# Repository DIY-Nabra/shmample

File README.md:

Sh'mample
=========

Sh'mample is a shift register driven sample and hold sequencer, capable of rungling.
Inspired in equal parts by the Ciat-Lonbarde Man with the Red Steam, and the Buchla 264.

For use with Ciat-Lonbarde instruments.

[Guide](assets/guide.md)

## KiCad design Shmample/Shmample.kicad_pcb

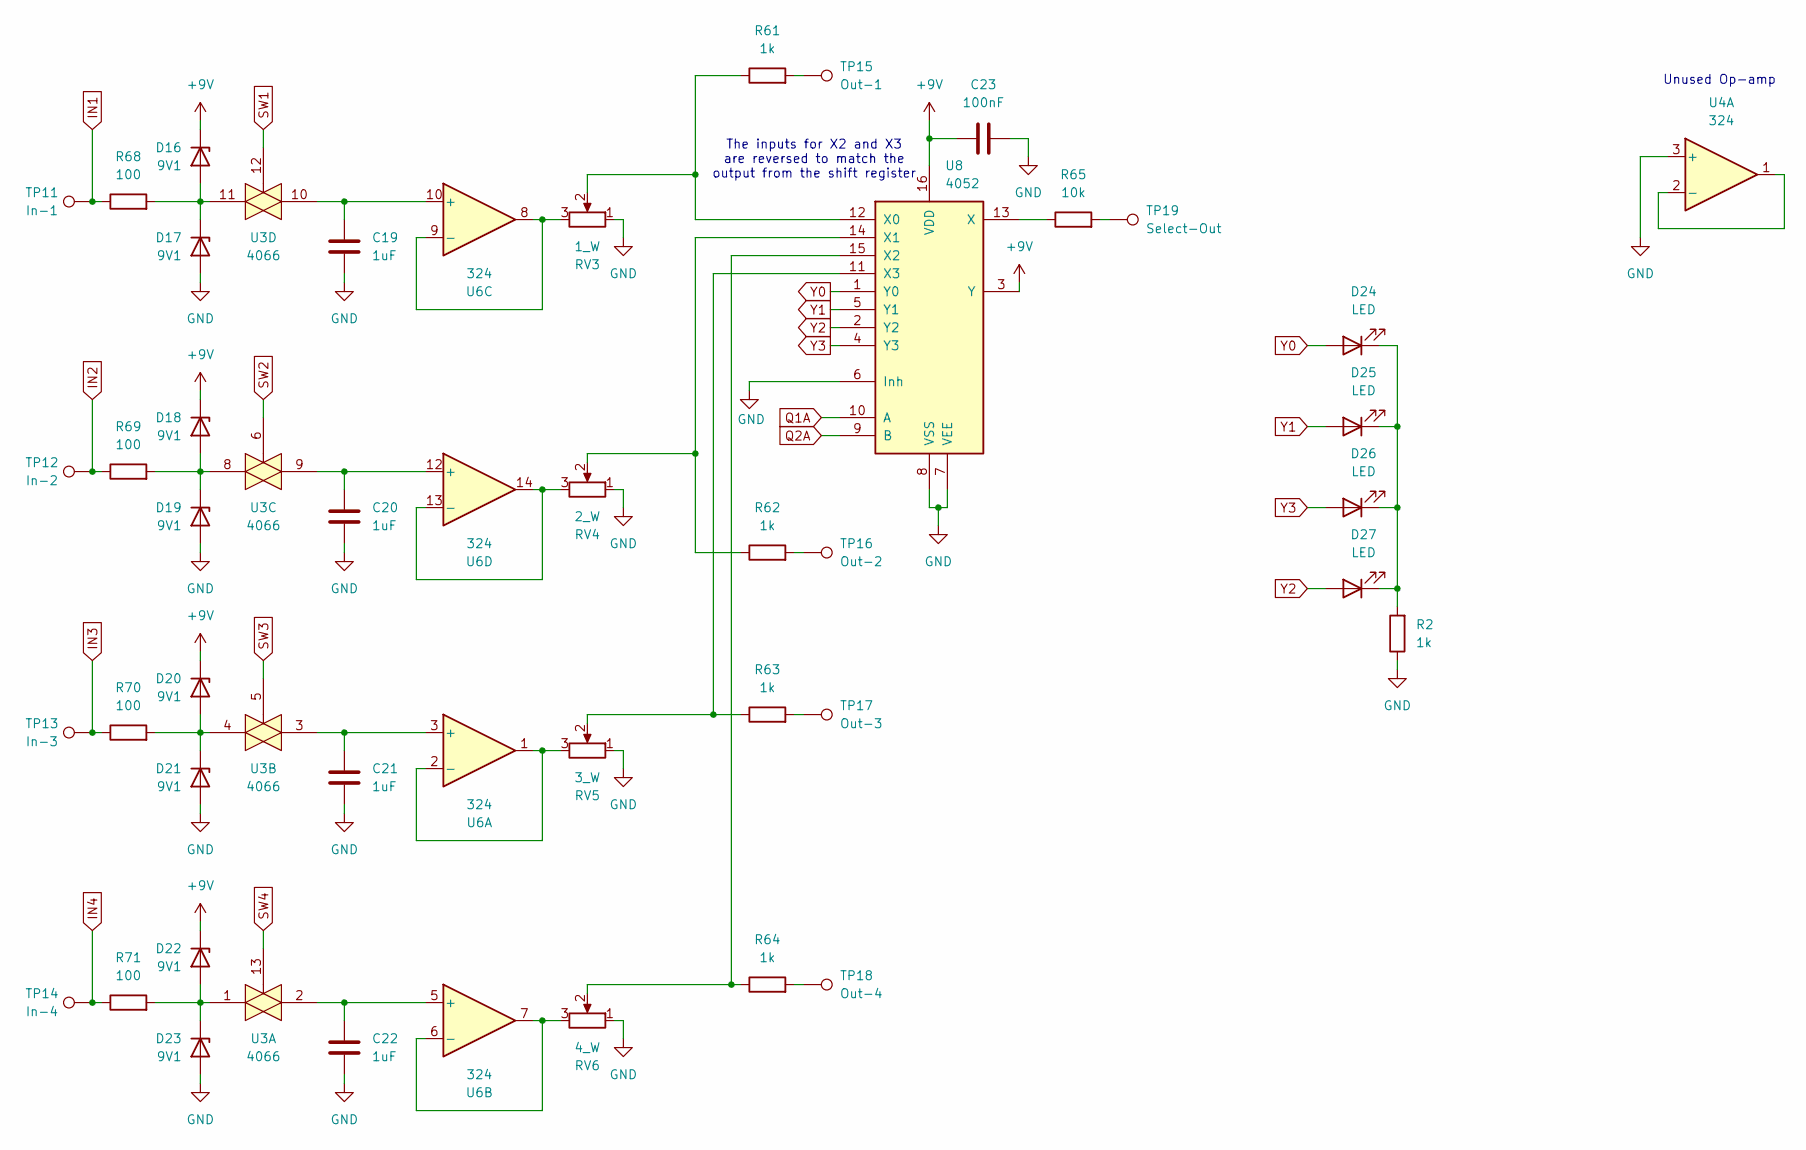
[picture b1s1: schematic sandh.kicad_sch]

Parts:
C19, C20, C21, C22: 1uF; cpoly105
C23: 100nF; cpoly104_small
D16, D17, D18, D19, D20, D21, D22, D23: 9V1; doz3
D24, D25, D26, D27: LED; led
R2, R61, R62, R63, R64: 1k; r3
R65: 10k; r3
R68, R69, R70, R71: 100; r3
RV3: 1_W; wnob1
RV4: 2_W; wnob2
RV5: 3_W; wnob3
RV6: 4_W; wnob4
TP11: In-1; wsquin
TP12: In-2; wsqout
TP13: In-3; wsqu3in
TP14: In-4; wsqu4in
TP15: Out-1; wtrin
TP16: Out-2; wtrin2
TP17: Out-3; wtrin3
TP18: Out-4; wtrin4
TP19: Select-Out; wsqout
U3: 4066; dip14
U4, U6: 324; dip14
U8: 4052; dip16

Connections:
+9V: C23.1, D16.1 (K), D18.1 (K), D20.1 (K), D22.1 (K), U8.3 (Y), U8.16 (VDD); also elsewhere on the board
GND: C19.2, C20.2, C21.2, C22.2, C23.2, D17.2 (A), D19.2 (A), D21.2 (A), D23.2 (A), R2.1, RV3.1, RV4.1, RV5.1, RV6.1, U4.3 (+), U8.6 (Inh), U8.7 (VEE), U8.8 (VSS); also elsewhere on the board
IN1: R68.1, TP11.1
IN2: R69.1, TP12.1
IN3: R70.1, TP13.1
IN4: R71.1, TP14.1
unnamed: D16.2 (A), D17.1 (K), R68.2, U3.11
unnamed: D18.2 (A), D19.1 (K), R69.2, U3.8
unnamed: D20.2 (A), D21.1 (K), R70.2, U3.4
unnamed: D22.2 (A), D23.1 (K), R71.2, U3.1
unnamed: D24.1 (K), D25.1 (K), D26.1 (K), D27.1 (K), R2.2
unnamed: R61.2, TP15.1
unnamed: R62.2, TP16.1
unnamed: R63.2, TP17.1
unnamed: R64.2, TP18.1
unnamed: R65.2, TP19.1
unnamed: U4.1, U4.2 (-)
unnamed: C21.1, U3.3, U6.3 (+)
unnamed: RV5.3, U6.1, U6.2 (-)
unnamed: C22.1, U3.2, U6.5 (+)
unnamed: RV6.3, U6.6 (-), U6.7
unnamed: C19.1, U3.10, U6.10 (+)
unnamed: RV3.3, U6.8, U6.9 (-)
unnamed: C20.1, U3.9, U6.12 (+)
unnamed: RV4.3, U6.13 (-), U6.14
unnamed: R61.1, RV3.2, U8.12 (X0)
unnamed: R62.1, RV4.2, U8.14 (X1)
unnamed: R64.1, RV6.2, U8.15 (X2)
unnamed: R63.1, RV5.2, U8.11 (X3)
unnamed: R65.1, U8.13 (X)
Q1A: U8.10 (A); also elsewhere on the board
Q2A: U8.9 (B); also elsewhere on the board
SW1: U3.12; also elsewhere on the board
SW2: U3.6; also elsewhere on the board
SW3: U3.5; also elsewhere on the board
SW4: U3.13; also elsewhere on the board
Y0: D24.2 (A), U8.1 (Y0)
Y1: D25.2 (A), U8.5 (Y1)
Y2: D27.2 (A), U8.2 (Y2)
Y3: D26.2 (A), U8.4 (Y3)

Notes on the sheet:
The inputs for X2 and X3 are reversed to match the output from the shift register
Unused Op-amp

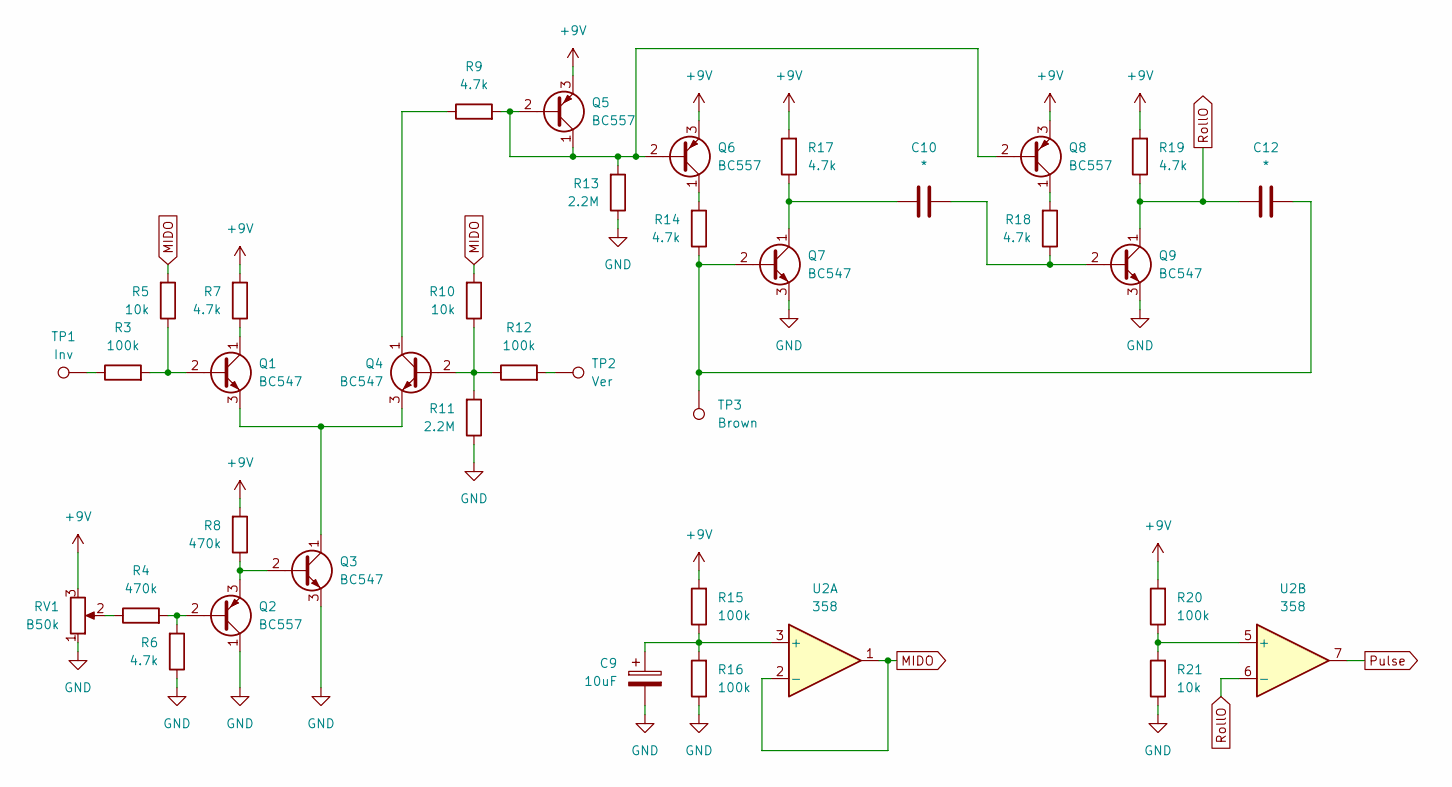
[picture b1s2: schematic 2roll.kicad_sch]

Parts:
C9: 10uF; cel1
C10, C12: *; chairy
Q1, Q3, Q4, Q7, Q9: BC547; qnpn
Q2, Q5, Q6, Q8: BC557; qpnp
R3, R12, R15, R16, R20: 100k; r3
R4, R8: 470k; r3
R5, R10, R21: 10k; r3
R6, R7, R9, R14, R17, R18, R19: 4.7k; r3
R11, R13: 2.2M; r3
RV1: B50k; wnob
TP1: Inv; wtrin2
TP2: Ver; wtrin
TP3: Brown; wsquin
U2: 358; dip8

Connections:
+9V: Q5.3 (E), Q6.3 (E), Q8.3 (E), R7.2, R8.2, R15.2, R17.2, R19.2, R20.2, RV1.3; also elsewhere on the board
GND: C9.2, Q2.1 (C), Q3.3 (E), Q7.3 (E), Q9.3 (E), R6.1, R11.1, R13.1, R16.1, R21.1, RV1.1; also elsewhere on the board
MIDO: R5.2, R10.2, U2.1, U2.2 (-); also elsewhere on the board
unnamed: Q1.2 (B), R3.2, R5.1
unnamed: Q1.1 (C), R7.1
unnamed: Q1.3 (E), Q3.1 (C), Q4.3 (E)
unnamed: Q2.2 (B), R4.2, R6.2
unnamed: Q2.3 (E), Q3.2 (B), R8.1
unnamed: Q4.2 (B), R10.1, R11.2, R12.1
unnamed: Q4.1 (C), R9.1
unnamed: Q5.1 (C), Q5.2 (B), Q6.2 (B), Q8.2 (B), R9.2, R13.2
unnamed: Q6.1 (C), R14.2
unnamed: C12.2, Q7.2 (B), R14.1, TP3.1
unnamed: C10.1, Q7.1 (C), R17.1
unnamed: Q8.1 (C), R18.2
unnamed: C10.2, Q9.2 (B), R18.1
unnamed: R3.1, TP1.1
unnamed: R4.1, RV1.2
unnamed: R12.2, TP2.1
unnamed: C9.1, R15.1, R16.2, U2.3 (+)
unnamed: R20.1, R21.2, U2.5 (+)
Pulse: U2.7; also elsewhere on the board
RollO: C12.1, Q9.1 (C), R19.1, U2.6 (-)

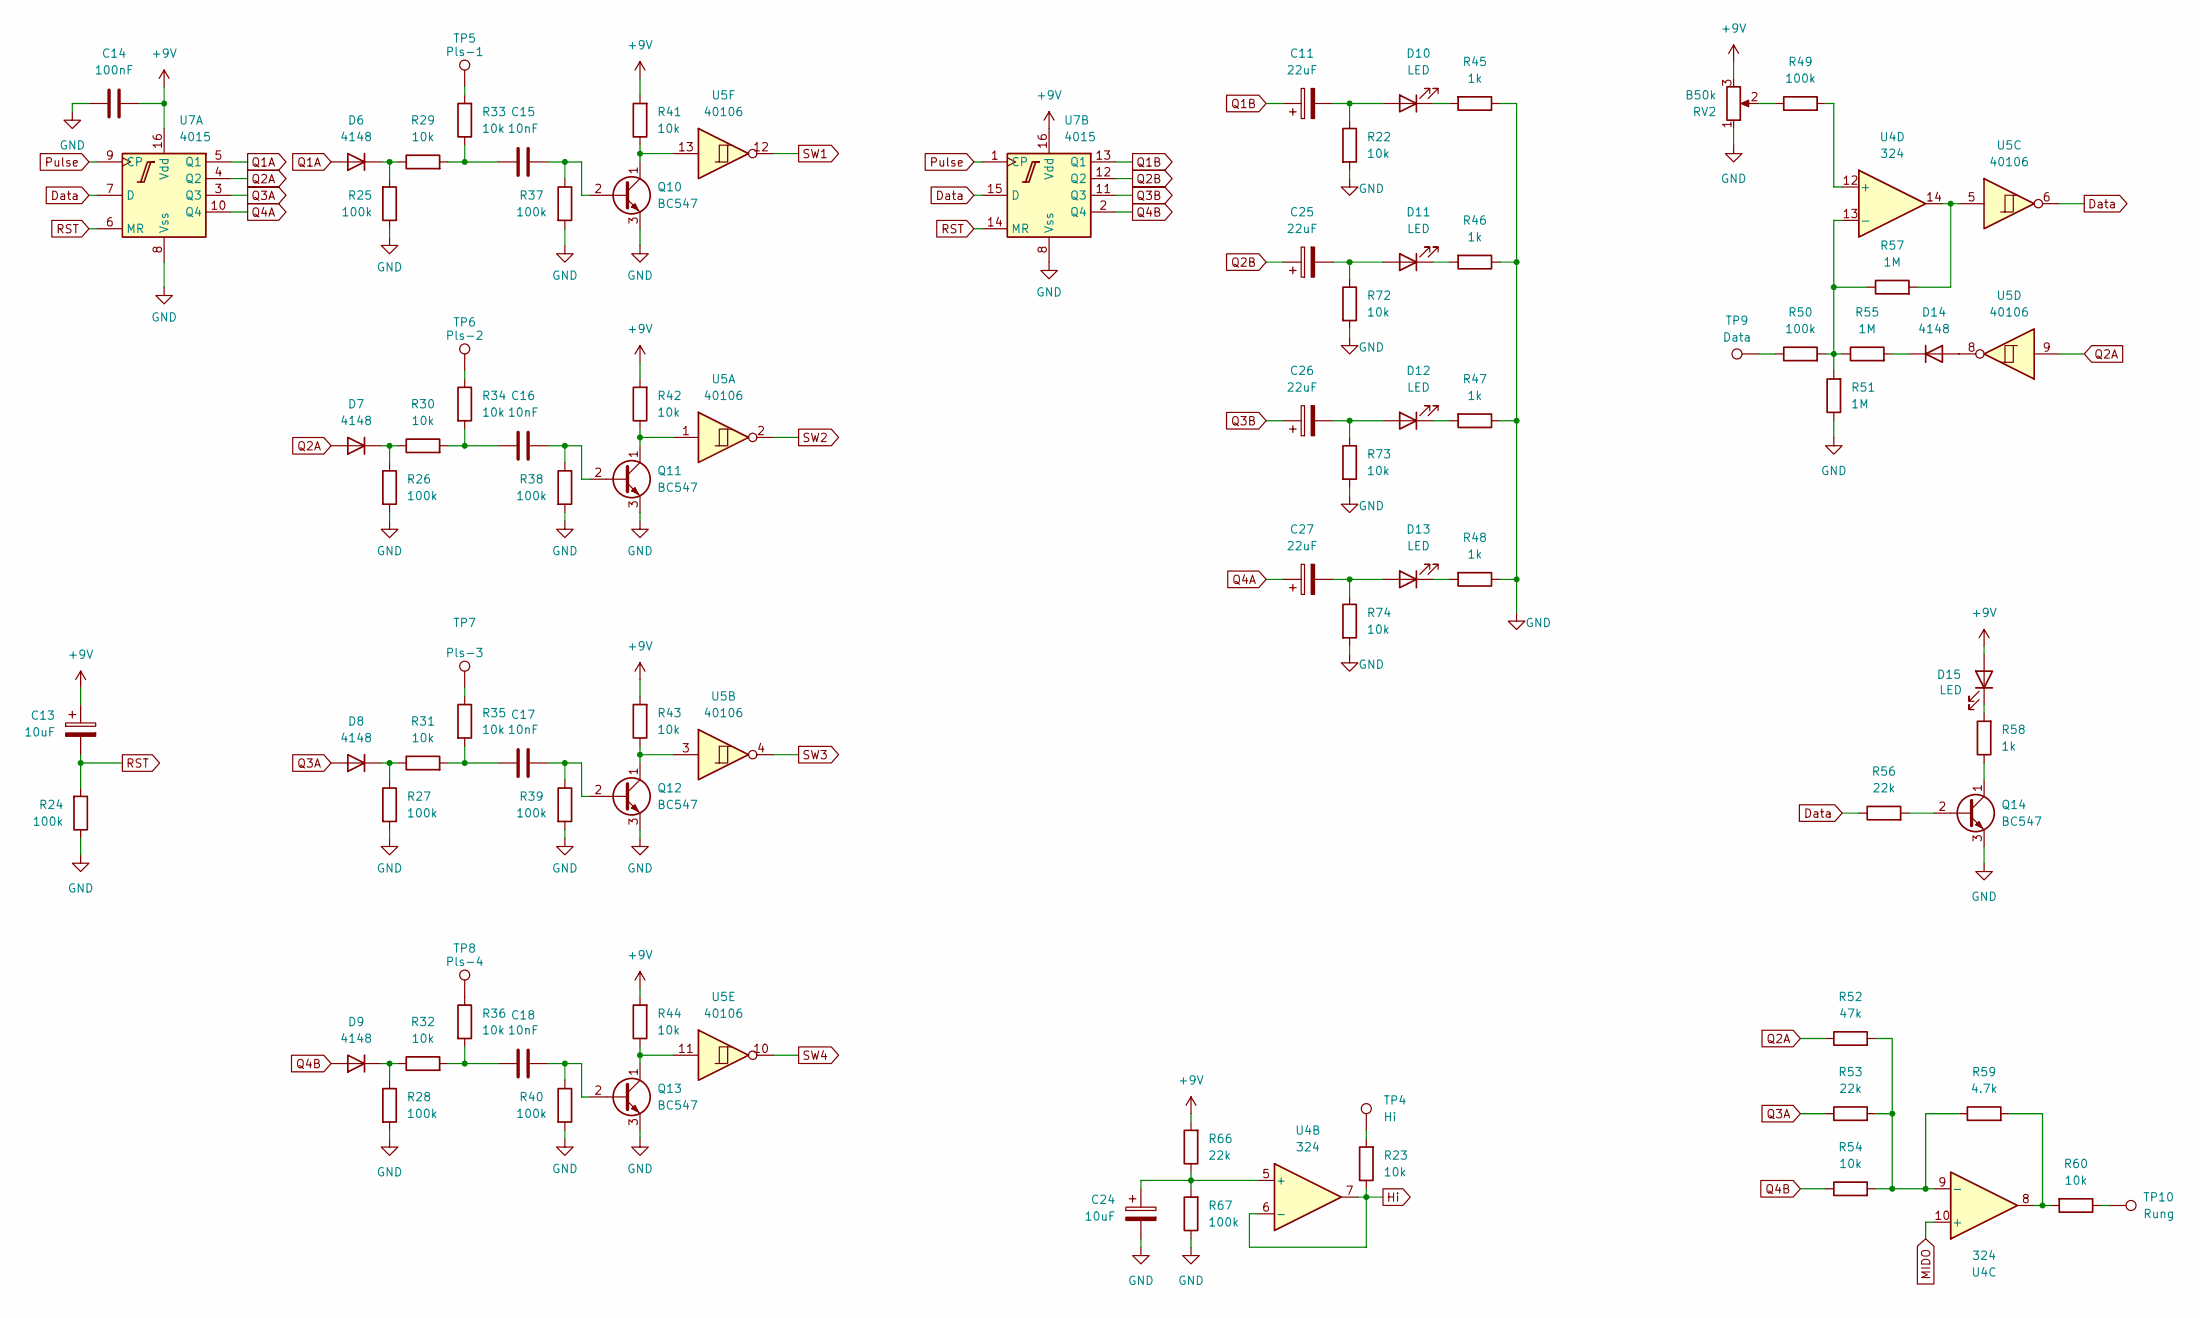
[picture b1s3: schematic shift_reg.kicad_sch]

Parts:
C11, C25, C26, C27: 22uF; cel1
C13, C24: 10uF; cel1
C14: 100nF; cpoly104_small
C15, C16, C17, C18: 10nF; cpoly103
D6, D7, D8, D9, D14: 4148; do3
D10, D11, D12, D13, D15: LED; led
Q10, Q11, Q12, Q13, Q14: BC547; qnpn
R22, R23, R29, R30, R31, R32, R33, R34, R35, R36, R41, R42, R43, R44, R54, R60, R72, R73, R74: 10k; r3
R24, R25, R26, R27, R28, R37, R38, R39, R40, R49, R50, R67: 100k; r3
R45, R46, R47, R48, R58: 1k; r3
R51, R55, R57: 1M; r3
R52: 47k; r3
R53, R56, R66: 22k; r3
R59: 4.7k; r3
RV2: B50k; wnob
TP4: Hi; wvout
TP5: Pls-1; wcircin
TP6: Pls-2; wcirc2in
TP7: Pls-3; wcirc3in
TP8: Pls-4; wcirc4in
TP9: Data; wtrin
TP10: Rung; wsqu2in
U4: 324; dip14
U5: 40106; dip14
U7: 4015; dip16

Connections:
+9V: C13.1, C14.2, D15.2 (A), R41.2, R42.2, R43.2, R44.2, R66.2, RV2.3, U7.16 (Vdd); also elsewhere on the board
Data: R56.1, U5.6, U7.7 (D), U7.15 (D)
GND: C14.1, C24.2, Q10.3 (E), Q11.3 (E), Q12.3 (E), Q13.3 (E), Q14.3 (E), R22.2, R24.1, R25.1, R26.2, R27.2, R28.2, R37.2, R38.2, R39.2, R40.2, R45.1, R46.1, R47.1, R48.1, R51.1, R67.1, R72.2, R73.2, R74.2, RV2.1, U7.8 (Vss); also elsewhere on the board
Hi: R23.1, U4.6 (-), U4.7
MIDO: U4.10 (+); also elsewhere on the board
unnamed: C15.1, R29.2, R33.1
unnamed: C16.1, R30.2, R34.2
unnamed: C17.1, R31.2, R35.2
unnamed: C18.1, R32.2, R36.2
unnamed: D6.1 (K), R25.2, R29.1
unnamed: D7.1 (K), R26.1, R30.1
unnamed: D8.1 (K), R27.1, R31.1
unnamed: D9.1 (K), R28.1, R32.1
unnamed: C11.2, D10.2 (A), R22.1
unnamed: D10.1 (K), R45.2
unnamed: C25.2, D11.2 (A), R72.1
unnamed: D11.1 (K), R46.2
unnamed: C26.2, D12.2 (A), R73.1
unnamed: D12.1 (K), R47.2
unnamed: C27.2, D13.2 (A), R74.1
unnamed: D13.1 (K), R48.2
unnamed: D14.2 (A), U5.8
unnamed: D14.1 (K), R55.2
unnamed: D15.1 (K), R58.2
unnamed: C15.2, Q10.2 (B), R37.1
unnamed: Q10.1 (C), R41.1, U5.13
unnamed: C16.2, Q11.2 (B), R38.1
unnamed: Q11.1 (C), R42.1, U5.1
unnamed: C17.2, Q12.2 (B), R39.1
unnamed: Q12.1 (C), R43.1, U5.3
unnamed: C18.2, Q13.2 (B), R40.1
unnamed: Q13.1 (C), R44.1, U5.11
unnamed: Q14.2 (B), R56.2
unnamed: Q14.1 (C), R58.1
unnamed: R23.2, TP4.1
unnamed: R33.2, TP5.1
unnamed: R34.1, TP6.1
unnamed: R35.1, TP7.1
unnamed: R36.1, TP8.1
unnamed: R49.1, RV2.2
unnamed: R50.1, TP9.1
unnamed: R57.2, U4.14, U5.5
unnamed: R59.2, R60.2, U4.8
unnamed: R60.1, TP10.1
unnamed: C24.1, R66.1, R67.2, U4.5 (+)
unnamed: R52.2, R53.2, R54.2, R59.1, U4.9 (-)
unnamed: R49.2, U4.12 (+)
unnamed: R50.2, R51.2, R55.1, R57.1, U4.13 (-)
Pulse: U7.1 (CP), U7.9 (CP); also elsewhere on the board
Q1A: D6.2 (A), U7.5 (Q1); also elsewhere on the board
Q1B: C11.1, U7.13 (Q1)
Q2A: D7.2 (A), R52.1, U5.9, U7.4 (Q2); also elsewhere on the board
Q2B: C25.1, U7.12 (Q2)
Q3A: D8.2 (A), R53.1, U7.3 (Q3)
Q3B: C26.1, U7.11 (Q3)
Q4A: C27.1, U7.10 (Q4)
Q4B: D9.2 (A), R54.1, U7.2 (Q4)
RST: C13.2, R24.2, U7.6 (MR), U7.14 (MR)
SW1: U5.12; also elsewhere on the board
SW2: U5.2; also elsewhere on the board
SW3: U5.4; also elsewhere on the board
SW4: U5.10; also elsewhere on the board

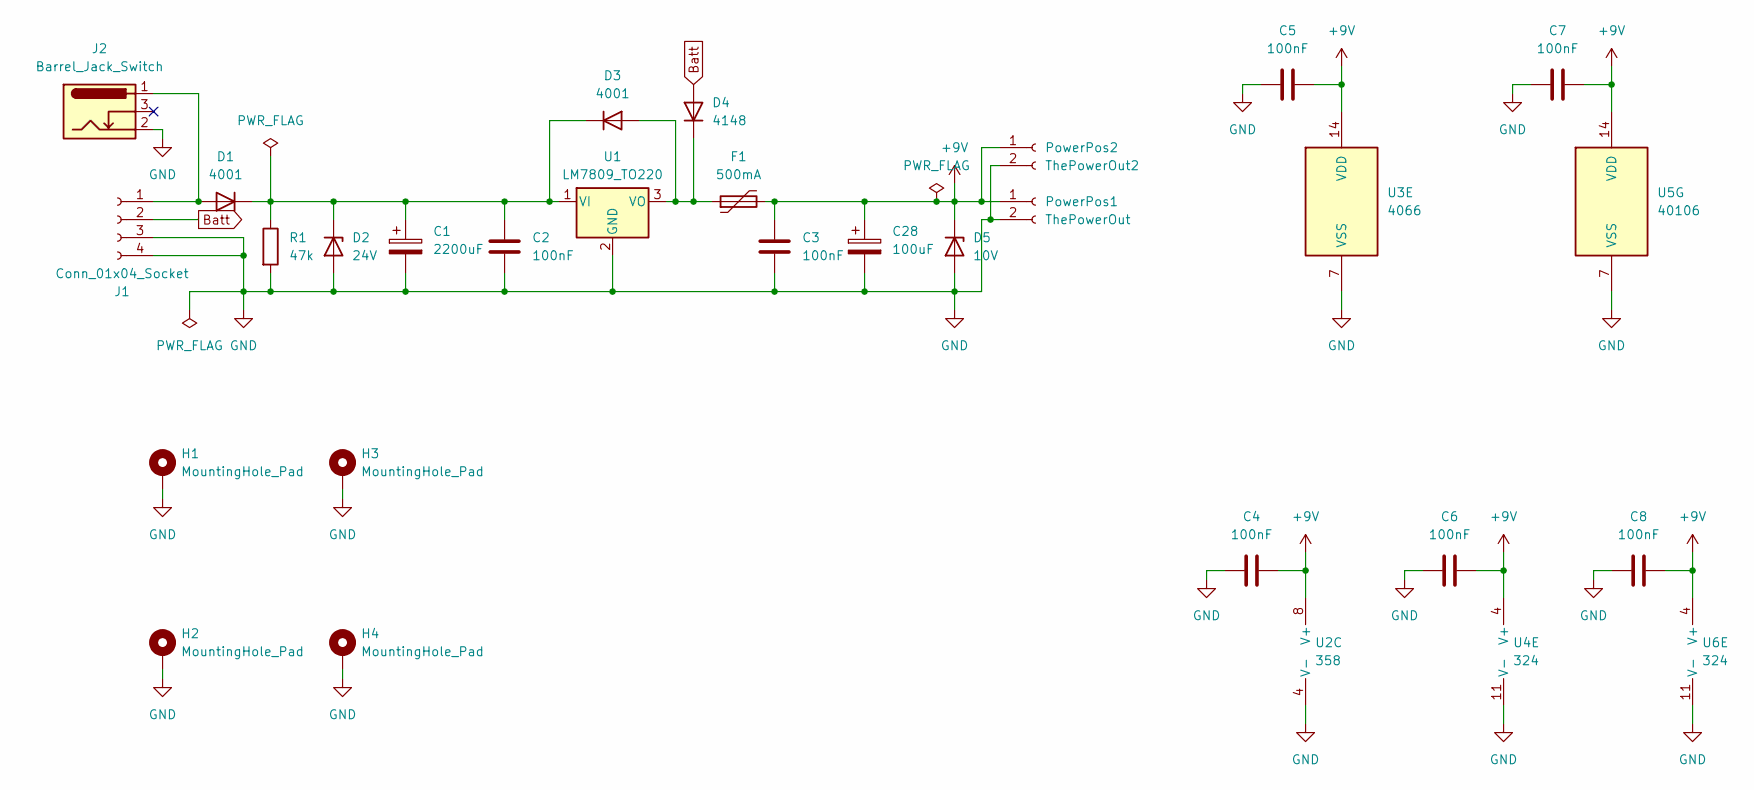
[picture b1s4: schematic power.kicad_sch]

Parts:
C1: 2200uF; cel2
C2, C3, C4, C5, C6, C7, C8: 100nF; cpoly104_small
C28: 100uF; cel2
D1, D3: 4001; do3
D2: 24V; doz3
D4: 4148; do3
D5: 10V; doz3
F1: 500mA; Fuse_Bourns_MF-RG500
H1, H2, H3, H4: MountingHole_Pad; MountingHole_3.2mm_M3_ISO7380_Pad
J1: Conn_01x04_Socket; powern
J2: Barrel_Jack_Switch; BarrelJack_Horizontal
PowerPos1: ThePowerOut; PinSocket_1x02_P2.54mm_Vertical
PowerPos2: ThePowerOut2; PinSocket_1x02_P2.54mm_Vertical
R1: 47k; r3
U1: LM7809_TO220; TO-220F-3_Horizontal_TabDown
U2: 358; dip8
U3: 4066; dip14
U4, U6: 324; dip14
U5: 40106; dip14

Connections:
+9V: C3.1, C4.2, C5.2, C6.2, C7.2, C8.2, C28.1, D5.1 (K), F1.2, PowerPos1.1, PowerPos2.1, U2.8 (V+), U3.14 (VDD), U4.4 (V+), U5.14 (VDD), U6.4 (V+); also elsewhere on the board
Batt: D4.2 (A), J1.2
GND: C1.2, C2.2, C3.2, C4.1, C5.1, C6.1, C7.1, C8.1, C28.2, D2.2 (A), D5.2 (A), H1.1, H2.1, H3.1, H4.1, J1.3, J1.4, J2.2, PowerPos1.2, PowerPos2.2, R1.2, U1.2 (GND), U2.4 (V-), U3.7 (VSS), U4.11 (V-), U5.7 (VSS), U6.11 (V-); also elsewhere on the board
unnamed: D1.2 (A), J1.1, J2.1
unnamed: C1.1, C2.1, D1.1 (K), D2.1 (K), D3.1 (K), R1.1, U1.1 (VI)
unnamed: D3.2 (A), D4.1 (K), F1.1, U1.3 (VO)

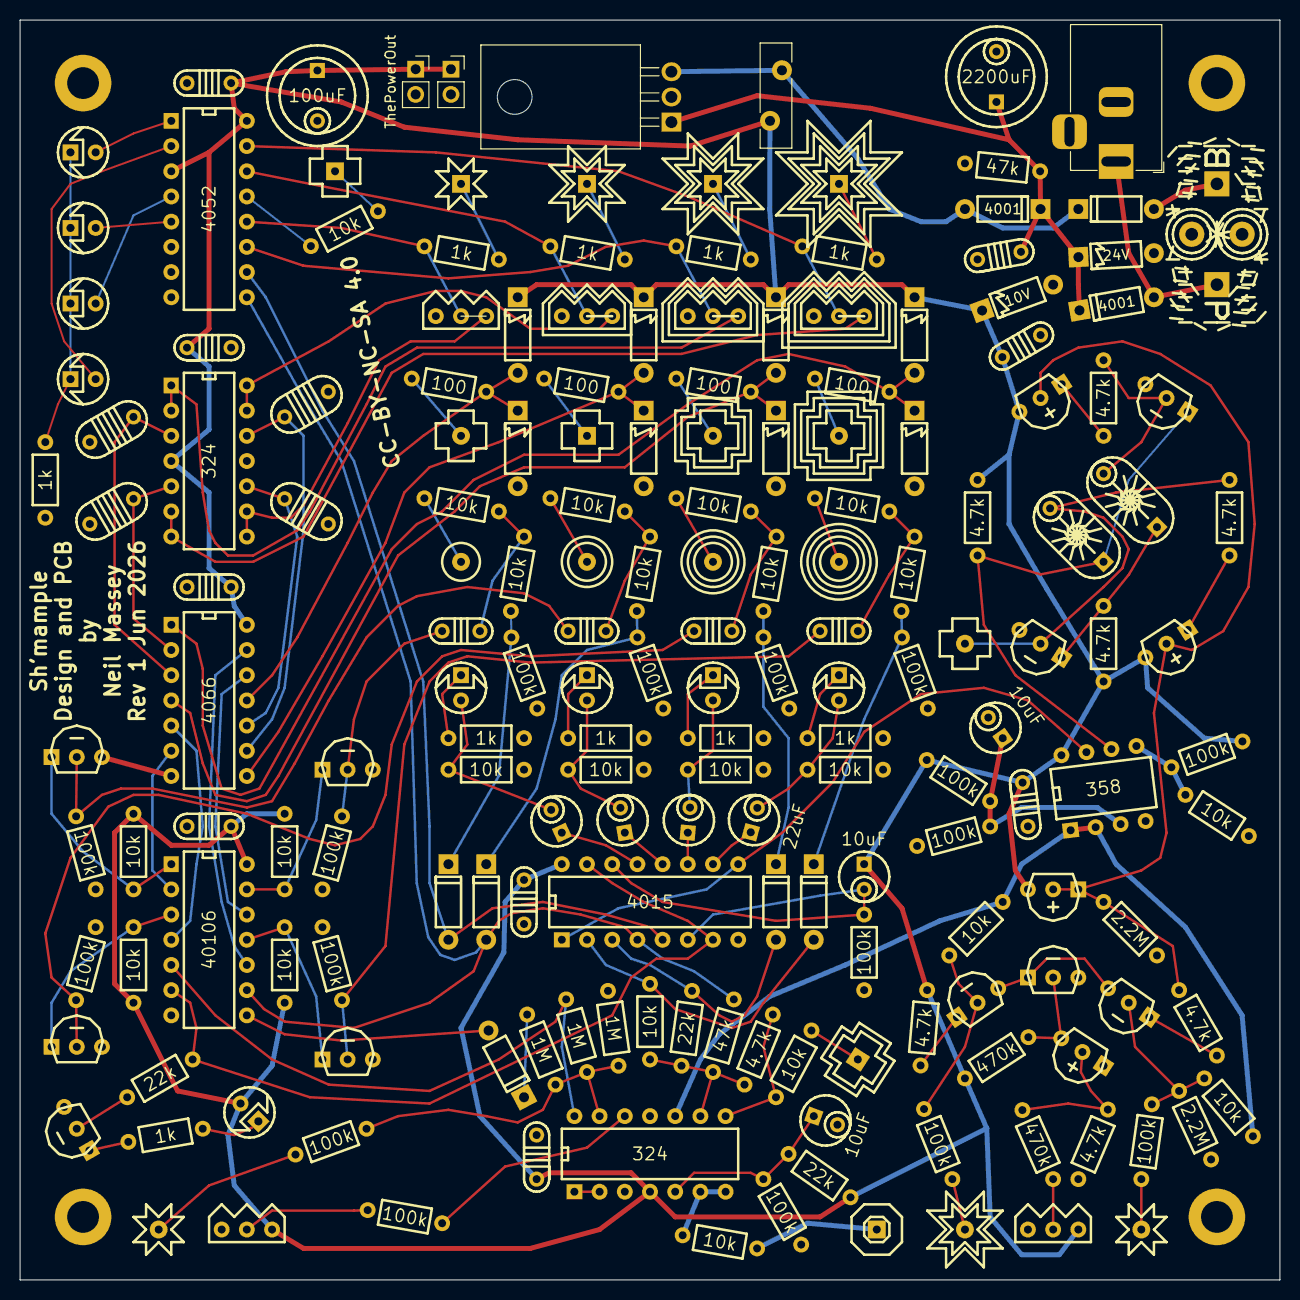
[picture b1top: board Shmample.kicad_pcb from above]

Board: 2 copper layers, 127.0 x 127.0 mm, 185 parts (0 on the bottom side), 117 nets.

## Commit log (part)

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2025-05-22 Moved Shmample
2025-06-02 Added attenuators
2025-06-05 Revision
2025-06-05 Rotated a pot. That is all
2025-06-05 Plussed up
2025-06-06 ironed out some kinky tracks
2025-11-24 Revision 1
2025-12-14 Big Pads
2025-12-21 Added shmatic
2025-12-21 updated guide for rev 1
2025-12-21 Just moved the rollz down a bit
2026-01-18 Final revision of revision 1 before manufacture

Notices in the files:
Shmample/Shmample.kicad_pcb:
CC-BY-NC-SA 4.0
